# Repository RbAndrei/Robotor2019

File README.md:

# Robotor2019
Robot electric schematics, PCBs and programs for team RaSky's participating robots in the international phase of Robotor.
Electric schematics and PCBs are made in KiCad, version 5.1.2_2 for 64-bit Windows, available for free at http://www.kicad-pcb.org/
Code written in the C programming language, with the help of the Arduino IDE, version 1.8.9 for Windows, available for free at https://www.arduino.cc/en/main/software

Everything made by the team members Casapu Denis Cristian and Roibu Andrei on Github.

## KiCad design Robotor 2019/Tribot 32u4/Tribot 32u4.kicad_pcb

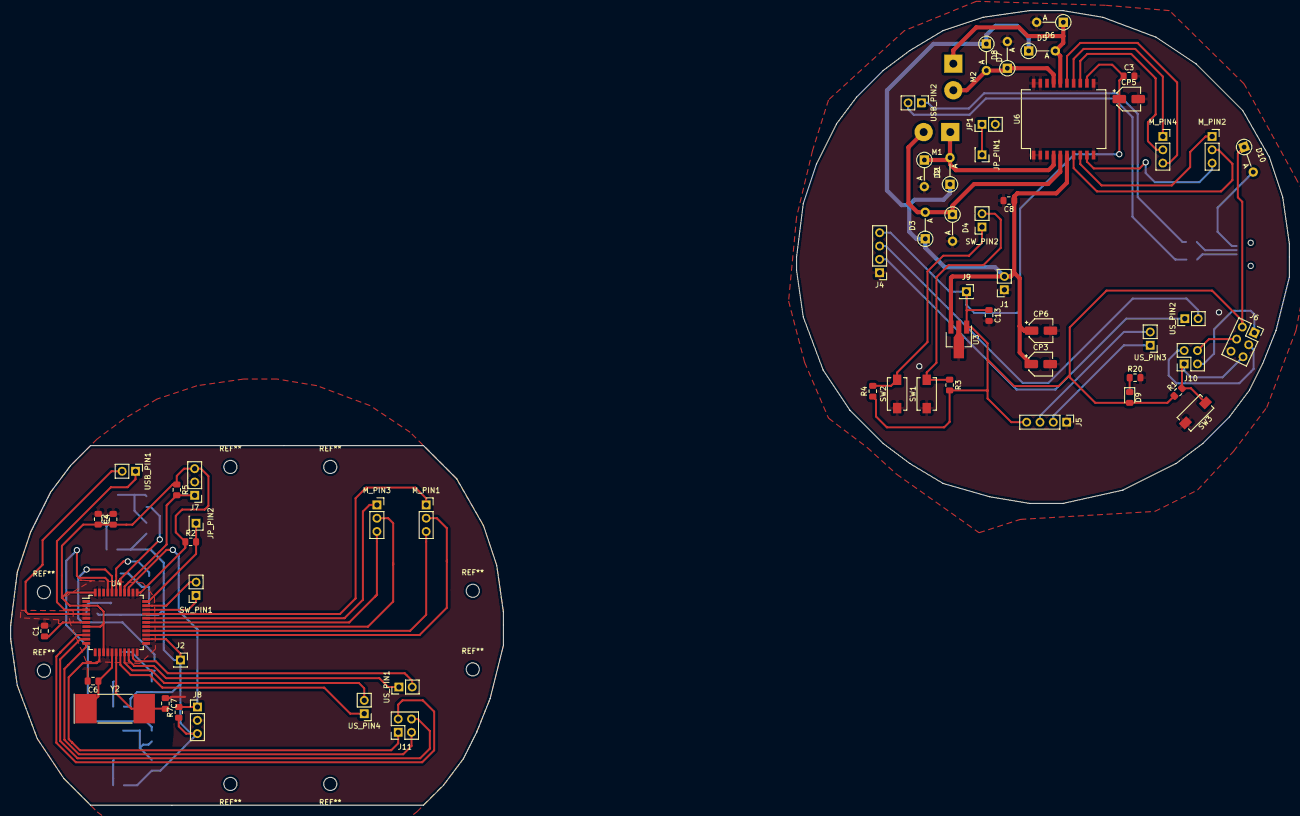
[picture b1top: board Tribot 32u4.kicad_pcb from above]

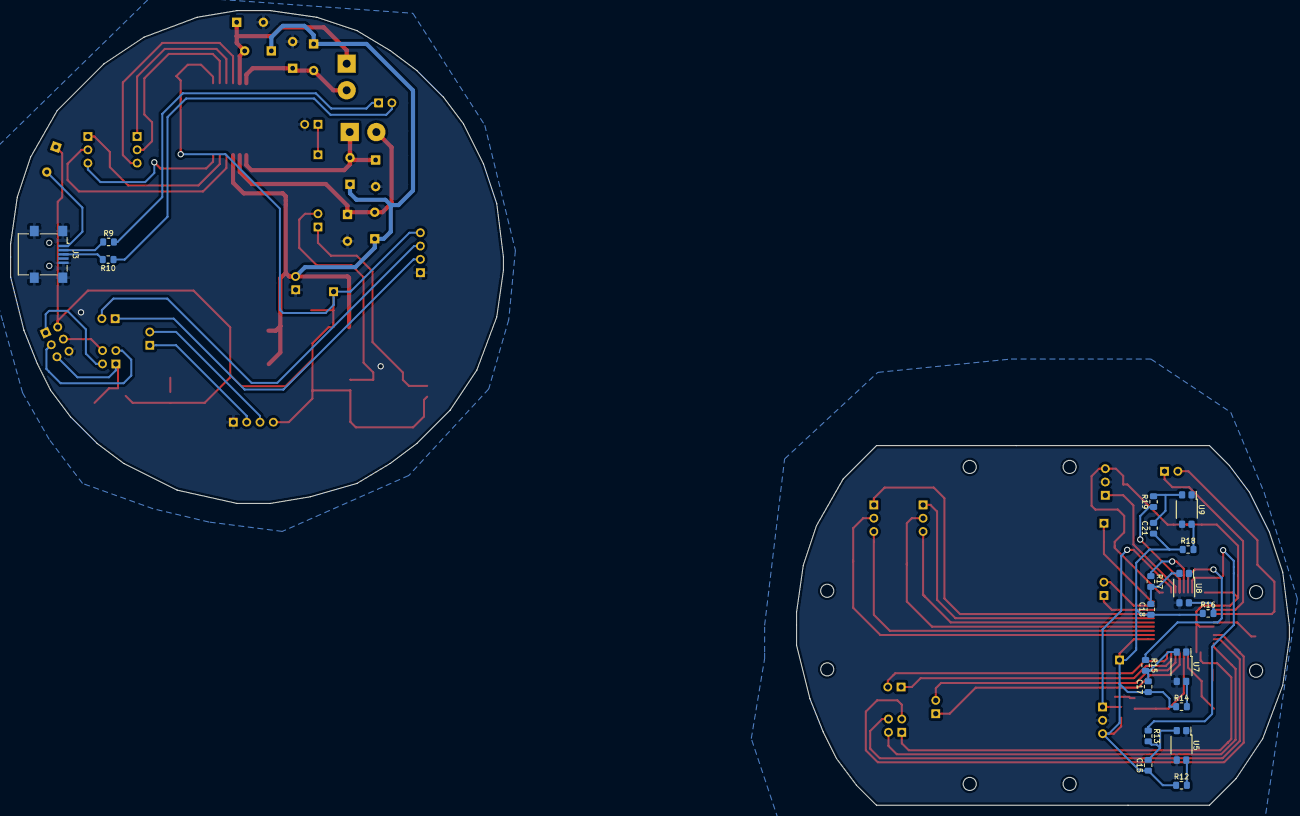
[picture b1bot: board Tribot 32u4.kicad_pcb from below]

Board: 2 copper layers, 243.9 x 151.5 mm, 81 parts (19 on the bottom side), 67 nets.

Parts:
C1: 1u; C_0805_2012Metric_Pad1.15x1.40mm_HandSolder
C2, C3, C4, C8, C13: 100n; C_0805_2012Metric_Pad1.15x1.40mm_HandSolder
C6, C7: 22p; C_0805_2012Metric_Pad1.15x1.40mm_HandSolder
C15, C17, C18, C21: 10n; C_0805_2012Metric_Pad1.15x1.40mm_HandSolder
CP3: 10uF; CP_Elec_4x5.3
CP5, CP6: 100uF; CP_Elec_4x5.3
D1, D2, D3, D4, D5, D6, D7, D8, D10: D; D_A-405_P5.08mm_Vertical_AnodeUp
D9: LED; LED_0805_2012Metric_Pad1.15x1.40mm_HandSolder
J1: Conn_01x03_Male; PinSocket_1x02_P2.54mm_Vertical
J2, J9: Conn_01x01; PinSocket_1x01_P2.54mm_Vertical
J3: USB_B_Mini; USB_Mini-B_Lumberg_2486_01_Horizontal
J4, J5: Conn_01x04_Female; PinHeader_1x04_P2.54mm_Vertical
J6: AVR-ISP-6; PinSocket_2x03_P2.54mm_Vertical
J7, J8: Conn_01x03_Female; PinHeader_1x03_P2.54mm_Vertical
J10, J11: Conn_01x04; PinSocket_2x02_P2.54mm_Vertical
JP1: Jumper; PinHeader_1x02_P2.54mm_Vertical
JP_PIN1, JP_PIN2: Conn_01x01; PinSocket_1x01_P2.54mm_Vertical
M1, M2: Motor_DC; SolderWirePad_1x02_P5.08mm_Drill1.5mm
M_PIN1, M_PIN2, M_PIN3, M_PIN4: Conn_01x03; PinSocket_1x03_P2.54mm_Vertical
R1, R3, R4: 10K; R_0805_2012Metric_Pad1.15x1.40mm_HandSolder
R2, R5, R7, R20: 1K; R_0805_2012Metric_Pad1.15x1.40mm_HandSolder
R9, R10: 22; R_0805_2012Metric_Pad1.15x1.40mm_HandSolder
R12, R13, R14, R15, R16, R17, R18, R19: 220; R_0805_2012Metric_Pad1.15x1.40mm_HandSolder
SW1, SW2, SW3: SW_Push; SW_SPST_EVQPE1
SW_PIN1, SW_PIN2: Conn_01x02; PinSocket_1x02_P2.54mm_Vertical
U3: AMS1117-5.0; SOT-89-3_Handsoldering
U4: ATMEGA32U4-AU; TQFP-44_10x10mm_P0.8mm
U5, U7, U8, U9: ITR8307; Everlight_ITR8307
U6: L298P; HSOP-20-1EP_11.0x15.9mm_P1.27mm_SlugUp
USB_PIN1, USB_PIN2: Conn_01x02; PinHeader_1x02_P2.54mm_Vertical
US_PIN1, US_PIN2, US_PIN3, US_PIN4: Conn_01x02; PinHeader_1x02_P2.54mm_Vertical
Y2: 8Mhz; Crystal_SMD_SeikoEpson_MA505-2Pin_12.7x5.1mm

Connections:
5V: C2.1, C4.2, C15.1, C17.1, C18.1, C21.1, J2.1, J7.3, J8.3, R2.1, R5.1, R7.1, R12.1, R14.1, R16.1, R18.1, U4.2, U4.7, U4.14, U4.24, U4.34, U4.44
+5V: C3.1, C13.1, CP5.1, D9.2, D10.1, J4.4, J5.4, J6.2, J9.1, R1.1, R3.2, R4.1, U3.1, U6.12
+7.5V: C8.1, CP3.1, CP6.1, D1.1, D3.1, D5.1, D7.1, J1.2, U3.3, U6.6
CRYSTAL1: C7.2, U4.17, Y2.2
CRYSTAL2: C6.1, U4.16, Y2.1
EnA: M_PIN2.1, U6.8
EnA_B: M_PIN1.1, U4.30
EnB: M_PIN4.1, U6.14
EnB_B: M_PIN3.1, U4.29
GND: C1.2, C2.2, C3.2, C4.1, C6.2, C7.1, C8.2, C13.2, CP3.2, CP5.2, CP6.2, D2.2, D4.2, D6.2, D8.2, J1.1, J3.5, J3.6, J4.1, J5.1, J6.6, J7.2, J8.2, JP1.2, R20.2, SW1.1, SW2.1, SW3.2, U3.2, U4.5, U4.15, U4.23, U4.35, U4.43, U5.1, U5.4, U6.1, U6.2, U6.10, U6.11, U6.19, U6.20, U7.1, U7.4, U8.1, U8.4, U9.1, U9.4
H1: J8.1, R7.2, U4.36
H2: J7.1, R5.2, U4.37
HWB: JP_PIN2.1, R2.2, U4.33
M1IN1: M_PIN2.2, U6.7
M1IN1_B: M_PIN1.2, U4.25
M1IN2: M_PIN2.3, U6.9
M1IN2_B: M_PIN1.3, U4.26
M2IN1: M_PIN4.2, U6.13
M2IN1_B: M_PIN3.2, U4.27
M2IN2: M_PIN4.3, U6.15
M2IN2_B: M_PIN3.3, U4.28
MISO: J6.1, J10.2
MISO_B: J11.2, U4.11
MOSI: J6.4, J10.4
MOSI_B: J11.4, U4.10
unnamed: C1.1, U4.6
unnamed: C15.2, R13.2, U5.3
unnamed: C17.2, R15.2, U7.3
unnamed: C18.2, R17.2, U8.3
unnamed: C21.2, R19.2, U9.3
unnamed: D1.2, D2.1, M1.1, U6.4
unnamed: D3.2, D4.1, M1.2, U6.5
unnamed: D5.2, D6.1, M2.1, U6.16
unnamed: D7.2, D8.1, M2.2, U6.17
unnamed: D9.1, R20.1
unnamed: D10.2, J3.1
unnamed: J3.2, R9.1
unnamed: J3.3, R10.2
unnamed: JP1.1, JP_PIN1.1
unnamed: R3.1, SW1.2, SW_PIN2.2
unnamed: R4.2, SW2.2, SW_PIN2.1
unnamed: R12.2, U5.2
unnamed: R14.2, U7.2
unnamed: R16.2, U8.2
unnamed: R18.2, U9.2
unnamed: SW_PIN1.1, U4.31
unnamed: SW_PIN1.2, U4.32
RST: J6.5, J10.1, R1.2, SW3.1
RST_B: J11.1, U4.13
S1: R13.1, U4.41
S2: R15.1, U4.40
S3: R17.1, U4.39
S4: R19.1, U4.38
SCK: J6.3, J10.3
SCK_B: J11.3, U4.9
US1P_IN: U4.21, US_PIN1.2
US1P_OUT: U4.20, US_PIN1.1
US1_IN: J4.3, US_PIN2.2
US1_OUT: J4.2, US_PIN2.1
US2P_IN: U4.19, US_PIN4.2
US2P_OUT: U4.18, US_PIN4.1
US2_IN: J5.3, US_PIN3.2
US2_OUT: J5.2, US_PIN3.1
USB+: U4.4, USB_PIN1.2
USB++: R10.1, USB_PIN2.2
USB-: U4.3, USB_PIN1.1
USB--: R9.2, USB_PIN2.1

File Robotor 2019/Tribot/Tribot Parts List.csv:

"Id";"Designator";"Package";"Quantity";"Designation";"Supplier and ref";
1;"M_PIN1,M_PIN3,M_PIN2,M_PIN4";"PinSocket_1x03_P2.54mm_Vertical";4;"Conn_01x03";;;
2;"REF**,REF**,REF**,REF**,REF**,REF**,REF**,REF**";"MountingHole_2.5mm";8;"MountingHole_2.5mm";;;
3;"D10,D1,D2,D3,D4,D5,D6,D7,D8";"D_A-405_P5.08mm_Vertical_AnodeUp";9;"D";;;
4;"C4,C5";"C_0805_2012Metric_Pad1.15x1.40mm_HandSolder";2;"10p";;;
5;"U5,U9,U8,U7";"Everlight_ITR8307";4;"ITR8307";;;
6;"BOOT_PIN1,BOOT_PIN2,PRGRM_PIN1,PRGRM_PIN2,US_PIN1,US_PIN2,US_PIN3,US_PIN4,USB_PIN1,USB_PIN2";"PinHeader_1x02_P2.54mm_Vertical";10;"Conn_01x02";;;
7;"C1,C2,C3,C8,C9,C13";"C_0805_2012Metric_Pad1.15x1.40mm_HandSolder";6;"100n";;;
8;"C6,C7";"C_0805_2012Metric_Pad1.15x1.40mm_HandSolder";2;"22p";;;
9;"C15,C17,C18,C21";"C_0805_2012Metric_Pad1.15x1.40mm_HandSolder";4;"10n";;;
10;"CP2,CP3";"CP_Elec_4x5.3";2;"10uF";;;
11;"CP4";"CP_Elec_4x5.3";1;"220uF";;;
12;"CP5,CP6";"CP_Elec_4x5.3";2;"100uF";;;
13;"D9";"LED_0805_2012Metric_Pad1.15x1.40mm_HandSolder";1;"LED";;;
14;"J1";"SolderWirePad_1x03_P5.715mm_Drill2mm";1;"Conn_01x03_Male";;;
15;"J2";"PinSocket_1x04_P2.54mm_Vertical";1;"Conn_01x04_Female";;;
16;"J3";"USB_Mini-B_Lumberg_2486_01_Horizontal";1;"USB_B_Mini";;;
17;"J4,J5";"PinHeader_1x04_P2.54mm_Vertical";2;"Conn_01x04_Female";;;
18;"J7,J8";"PinHeader_1x03_P2.54mm_Vertical";2;"Conn_01x03_Female";;;
19;"JP1,JP2";"PinSocket_1x02_P2.54mm_Vertical";2;"Jumper";;;
20;"M1,M2";"SolderWirePad_1x02_P5.08mm_Drill1.5mm";2;"Motor_DC";;;
21;"R1,R4,R8";"R_0805_2012Metric_Pad1.15x1.40mm_HandSolder";3;"10K";;;
22;"R2,R6,R9,R10";"R_0805_2012Metric_Pad1.15x1.40mm_HandSolder";4;"1R";;;
23;"R3";"R_0805_2012Metric_Pad1.15x1.40mm_HandSolder";1;"1K5";;;
24;"R5,R7";"R_0805_2012Metric_Pad1.15x1.40mm_HandSolder";2;"1K";;;
25;"R11";"R_0805_2012Metric_Pad1.15x1.40mm_HandSolder";1;"100k";;;
26;"R12,R13,R14,R15,R16,R17,R18,R19";"R_0805_2012Metric_Pad1.15x1.40mm_HandSolder";8;"220";;;
27;"R20";"R_0805_2012Metric_Pad1.15x1.40mm_HandSolder";1;"R";;;
28;"U1";"SOT-223-3_TabPin2";1;"AMS1117-3V3";;;
29;"U3";"SOT-223-3_TabPin2";1;"AMS1117-5.0";;;
30;"U4";"LQFP-48_7x7mm_P0.5mm";1;"STM32F103C8Tx";;;
31;"U6";"HSOP-20-1EP_11.0x15.9mm_P1.27mm_SlugUp";1;"L298P";;;
32;"Y1";"Crystal_SMD_SeikoEpson_MA505-2Pin_12.7x5.1mm";1;"32.768Khz";;;
33;"Y2";"Crystal_SMD_SeikoEpson_MA505-2Pin_12.7x5.1mm";1;"8Mhz";;;
34;"V_PIN1,V_PIN2";"SolderWirePad_1x02_P5.08mm_Drill1.5mm";2;"Conn_01x02";;;
35;"SW1,SW2";"SW_Push_1P1T_NO_6x6mm_H9.5mm";2;"SW_Push";;;
36;"SW_PIN1,SW_PIN2";"PinSocket_1x02_P2.54mm_Vertical";2;"Conn_01x02";;;

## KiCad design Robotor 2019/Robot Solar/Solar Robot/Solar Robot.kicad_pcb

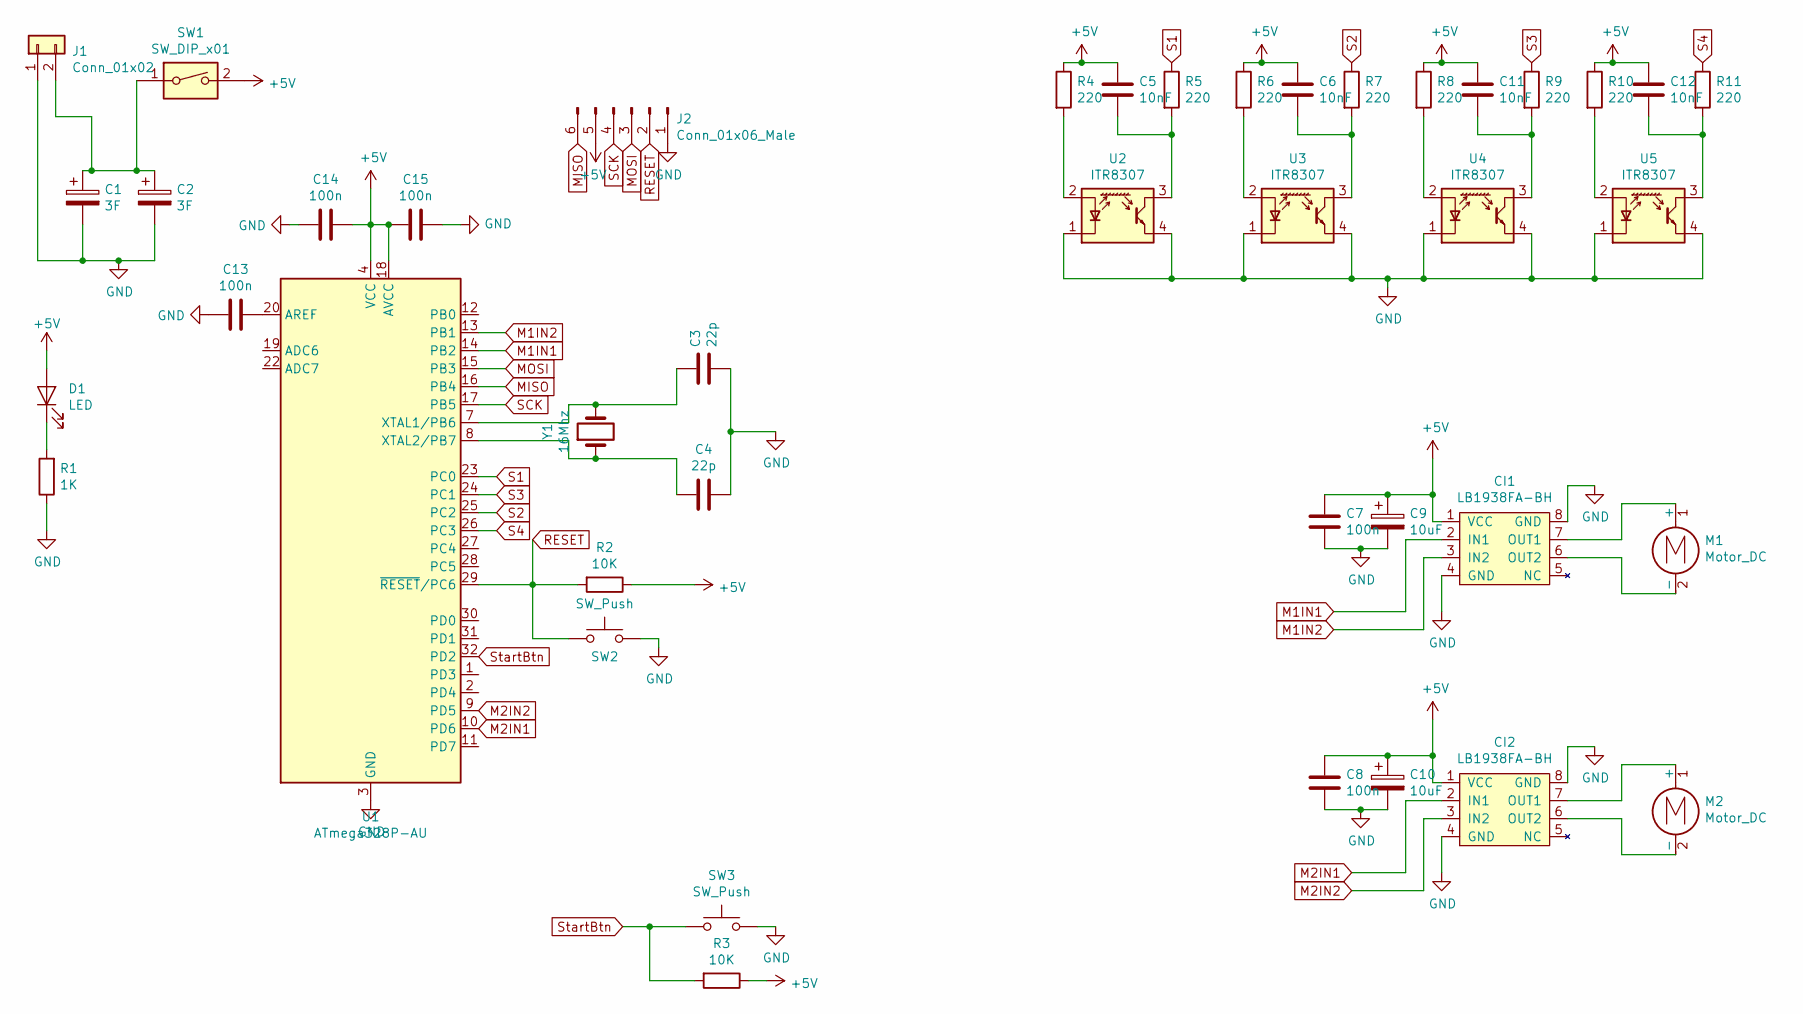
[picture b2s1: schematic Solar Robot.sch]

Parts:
C1, C2: 3F; CP_Radial_D8.0mm_P5.00mm
C3, C4: 22p; C_0805_2012Metric_Pad1.15x1.40mm_HandSolder
C5, C6, C11, C12: 10nF; C_0805_2012Metric_Pad1.15x1.40mm_HandSolder
C7, C8, C13, C14, C15: 100n; C_0805_2012Metric_Pad1.15x1.40mm_HandSolder
C9, C10: 10uF; CP_Elec_4x5.3
CI1, CI2: LB1938FA-BH; OnSemi_Micro8
D1: LED; LED_0805_2012Metric_Pad1.15x1.40mm_HandSolder
J1: Conn_01x02; SolderWirePad_1x02_P7.62mm_Drill2mm
J2: Conn_01x06_Male; PinSocket_2x03_P2.54mm_Vertical
M1, M2: Motor_DC; SolderWirePad_1x02_P5.08mm_Drill1.5mm
R1: 1K; R_0805_2012Metric_Pad1.15x1.40mm_HandSolder
R2, R3: 10K; R_0805_2012Metric_Pad1.15x1.40mm_HandSolder
R4, R5, R6, R7, R8, R9, R10, R11: 220; R_0805_2012Metric_Pad1.15x1.40mm_HandSolder
SW1: SW_DIP_x01; SolderWirePad_1x02_P5.08mm_Drill1.5mm
SW2, SW3: SW_Push; SW_SPST_CK_RS282G05A3
U1: ATmega328P-AU; TQFP-32_7x7mm_P0.8mm
U2, U3, U4, U5: ITR8307; Everlight_ITR8307
Y1: 16Mhz; Crystal_SMD_SeikoEpson_MA505-2Pin_12.7x5.1mm_HandSoldering

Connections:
+5V: C5.1, C6.1, C7.2, C8.2, C9.1, C10.1, C11.1, C12.1, C14.1, C15.2, CI1.1 (VCC), CI2.1 (VCC), D1.2 (A), J2.5, R2.1, R3.1, R4.1, R6.1, R8.1, R10.1, SW1.2, U1.4 (VCC), U1.6 (VCC), U1.18 (AVCC); also elsewhere on the board
GND: C1.2, C2.2, C3.2, C4.1, C7.1, C8.1, C9.2, C10.2, C13.2, C14.2, C15.1, CI1.4 (GND), CI1.8 (GND), CI2.4 (GND), CI2.8 (GND), J1.1, J2.1, R1.1, SW2.2, SW3.2, U1.3 (GND), U1.5 (GND), U1.21 (GND), U2.1 (K), U2.4 (E), U3.1 (K), U3.4 (E), U4.1 (K), U4.4 (E), U5.1 (K), U5.4 (E)
M1IN1: CI1.2 (IN1), U1.14 (PB2)
M1IN2: CI1.3 (IN2), U1.13 (PB1)
M2IN1: CI2.2 (IN1), U1.10 (PD6)
M2IN2: CI2.3 (IN2), U1.9 (PD5)
MISO: J2.6, U1.16 (PB4)
MOSI: J2.3, U1.15 (PB3)
unnamed: C1.1, C2.1, J1.2, SW1.1
unnamed: C3.1, U1.7 (XTAL1/PB6), Y1.2
unnamed: C4.2, U1.8 (XTAL2/PB7), Y1.1
unnamed 11: C5.2, R5.2, U2.3 (C); also elsewhere on the board
unnamed 12: C6.2, R7.2, U3.3 (C); also elsewhere on the board
unnamed 13: C11.2, R9.2, U4.3 (C); also elsewhere on the board
unnamed 14: C12.2, R11.2, U5.3 (C); also elsewhere on the board
unnamed: C13.1, U1.20 (AREF)
unnamed: CI1.6 (OUT2), M1.2 (-)
unnamed: CI1.7 (OUT1), M1.1 (+)
unnamed: CI2.6 (OUT2), M2.2 (-)
unnamed: CI2.7 (OUT1), M2.1 (+)
unnamed: D1.1 (K), R1.2
unnamed: R4.2, U2.2 (A)
unnamed: R6.2, U3.2 (A)
unnamed: R8.2, U4.2 (A)
unnamed: R10.2, U5.2 (A)
RESET: J2.2, R2.2, SW2.1, U1.29 (~RESET~/PC6)
S1: R5.1, U1.23 (PC0)
S2: R7.1, U1.25 (PC2)
S3: R9.1, U1.24 (PC1)
S4: R11.1, U1.26 (PC3)
SCK: J2.4, U1.17 (PB5)
StartBtn: R3.2, SW3.1, U1.32 (PD2)

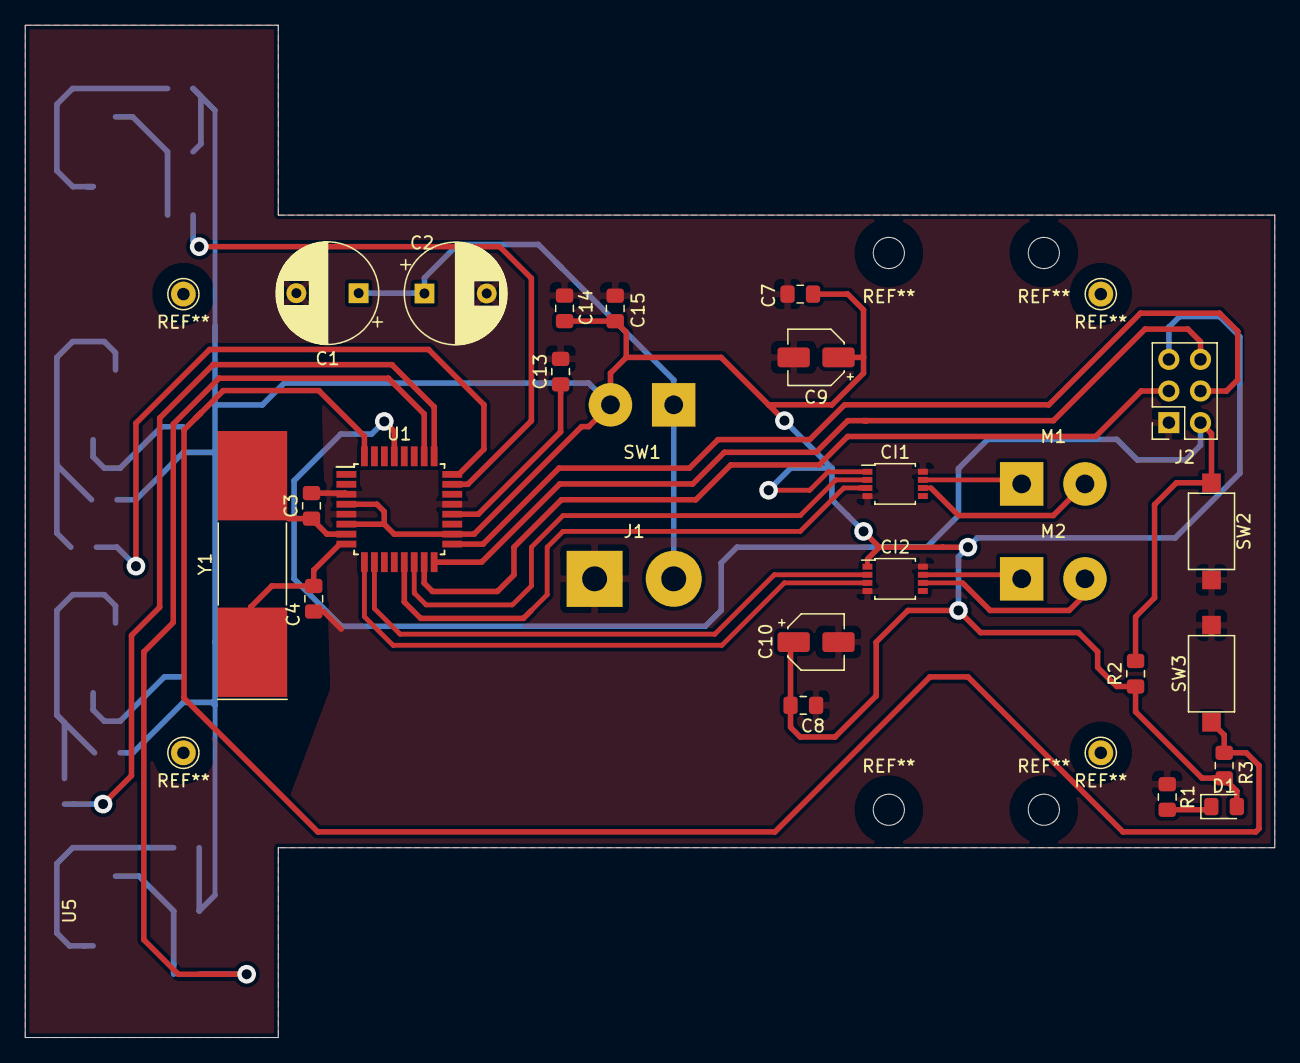
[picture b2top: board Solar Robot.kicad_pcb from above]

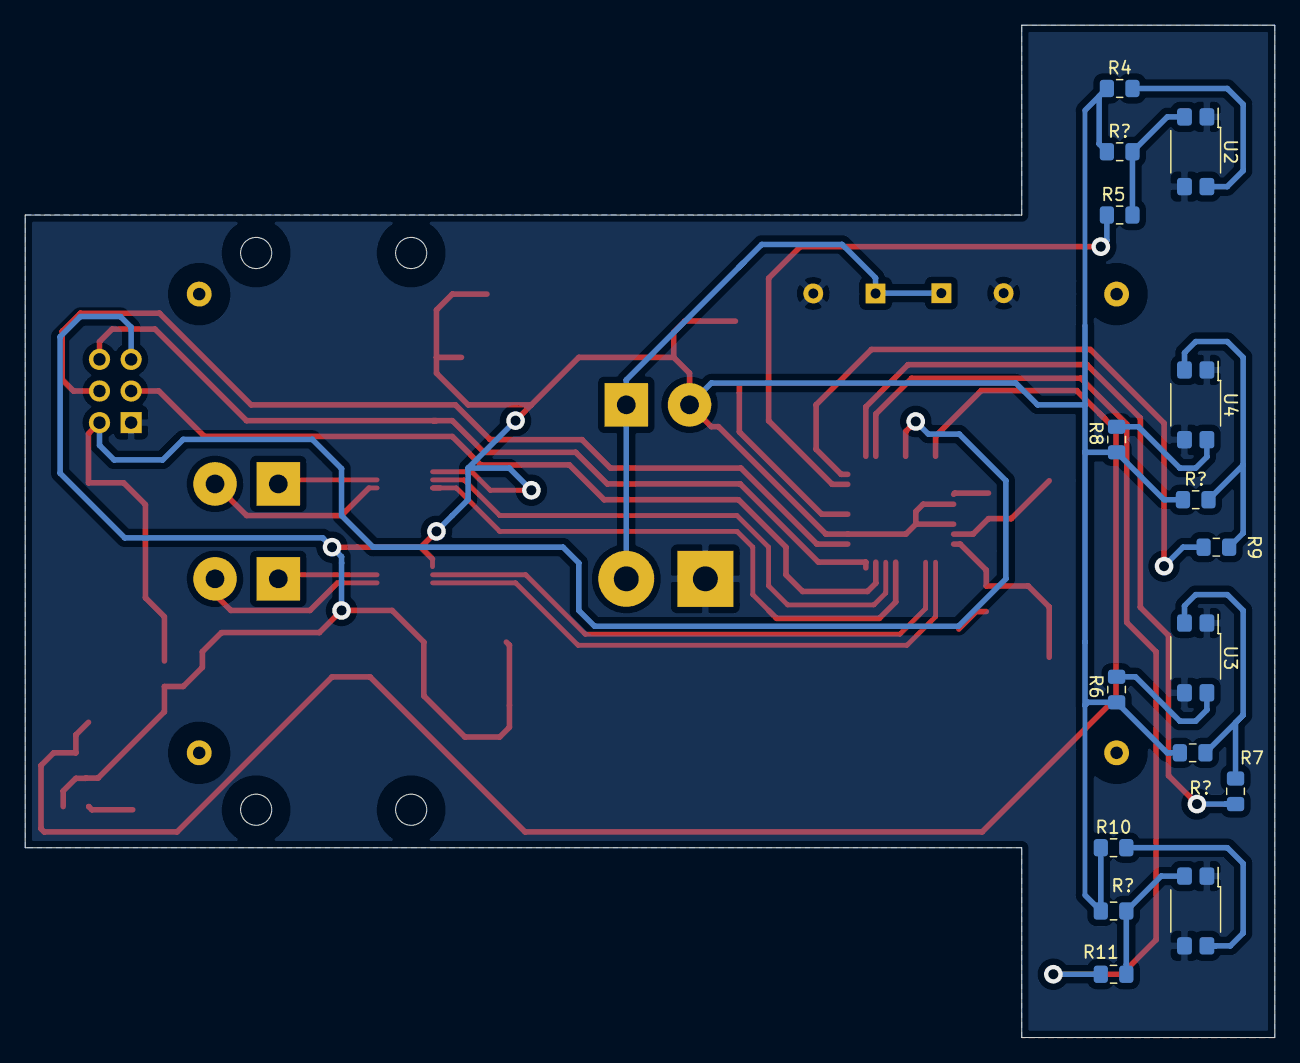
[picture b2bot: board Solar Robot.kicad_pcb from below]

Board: 2 copper layers, 100.3 x 81.3 mm, 42 parts (16 on the bottom side), 32 nets.

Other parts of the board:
R?: 47K; C_0805_2012Metric_Pad1.15x1.40mm_HandSolder
R?#2, R?#3, R?#4: 47K; C_0805_2012Metric_Pad1.15x1.40mm_HandSolder

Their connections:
+5V: R?.1, R?#2.1, R?#3.1, R?#4.1; also elsewhere on the board
unnamed 11: R?.2; also elsewhere on the board
unnamed 12: R?#2.2; also elsewhere on the board
unnamed 13: R?#3.2; also elsewhere on the board
unnamed 14: R?#4.2; also elsewhere on the board

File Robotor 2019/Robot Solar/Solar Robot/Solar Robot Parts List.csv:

"Id";"Designator";"Package";"Quantity";"Designation";"Supplier and ref";
1;"REF**,REF**,REF**,REF**";"Pin_D1.0mm_L10.0mm";4;"Pin_D1.0mm_L10.0mm";;;
2;"REF**,REF**,REF**,REF**";"MountingHole_2.5mm";4;"MountingHole_2.5mm";;;
3;"U2,U5,U3,U4";"Everlight_ITR8307";4;"ITR8307";;;
4;"C1,C2";"CP_Radial_D8.0mm_P5.00mm";2;"3F";;;
5;"C3,C4";"C_0805_2012Metric_Pad1.15x1.40mm_HandSolder";2;"22p";;;
6;"C5,C6,C11,C12";"C_0805_2012Metric_Pad1.15x1.40mm_HandSolder";4;"10nF";;;
7;"C7,C8";"C_0805_2012Metric_Pad1.15x1.40mm_HandSolder";2;"100n";;;
8;"C9,C10";"CP_Elec_4x5.3";2;"10uF";;;
9;"CI1,CI2";"OnSemi_Micro8";2;"LB1938FA-BH";;;
10;"D1";"LED_0805_2012Metric_Pad1.15x1.40mm_HandSolder";1;"LED";;;
11;"J1";"SolderWirePad_1x02_P7.62mm_Drill2mm";1;"Conn_01x02";;;
12;"J2";"PinHeader_1x06_P2.54mm_Vertical";1;"Conn_01x06_Male";;;
13;"M1,M2";"SolderWirePad_1x02_P5.08mm_Drill1.5mm";2;"Motor_DC";;;
14;"R1";"R_0805_2012Metric_Pad1.15x1.40mm_HandSolder";1;"1K";;;
15;"R2,R3";"R_0805_2012Metric_Pad1.15x1.40mm_HandSolder";2;"10K";;;
16;"R4,R5,R6,R7,R8,R9,R10,R11";"R_0805_2012Metric_Pad1.15x1.40mm_HandSolder";8;"220";;;
17;"SW1";"SolderWirePad_1x02_P5.08mm_Drill1.5mm";1;"SW_DIP_x01";;;
18;"SW2,SW3";"SW_Push_1P1T_NO_6x6mm_H9.5mm";2;"SW_Push";;;
19;"U1";"TQFP-32_7x7mm_P0.8mm";1;"ATmega328-PU";;;
20;"Y1";"Crystal_SMD_SeikoEpson_MA505-2Pin_12.7x5.1mm_HandSoldering";1;"16Mhz";;;

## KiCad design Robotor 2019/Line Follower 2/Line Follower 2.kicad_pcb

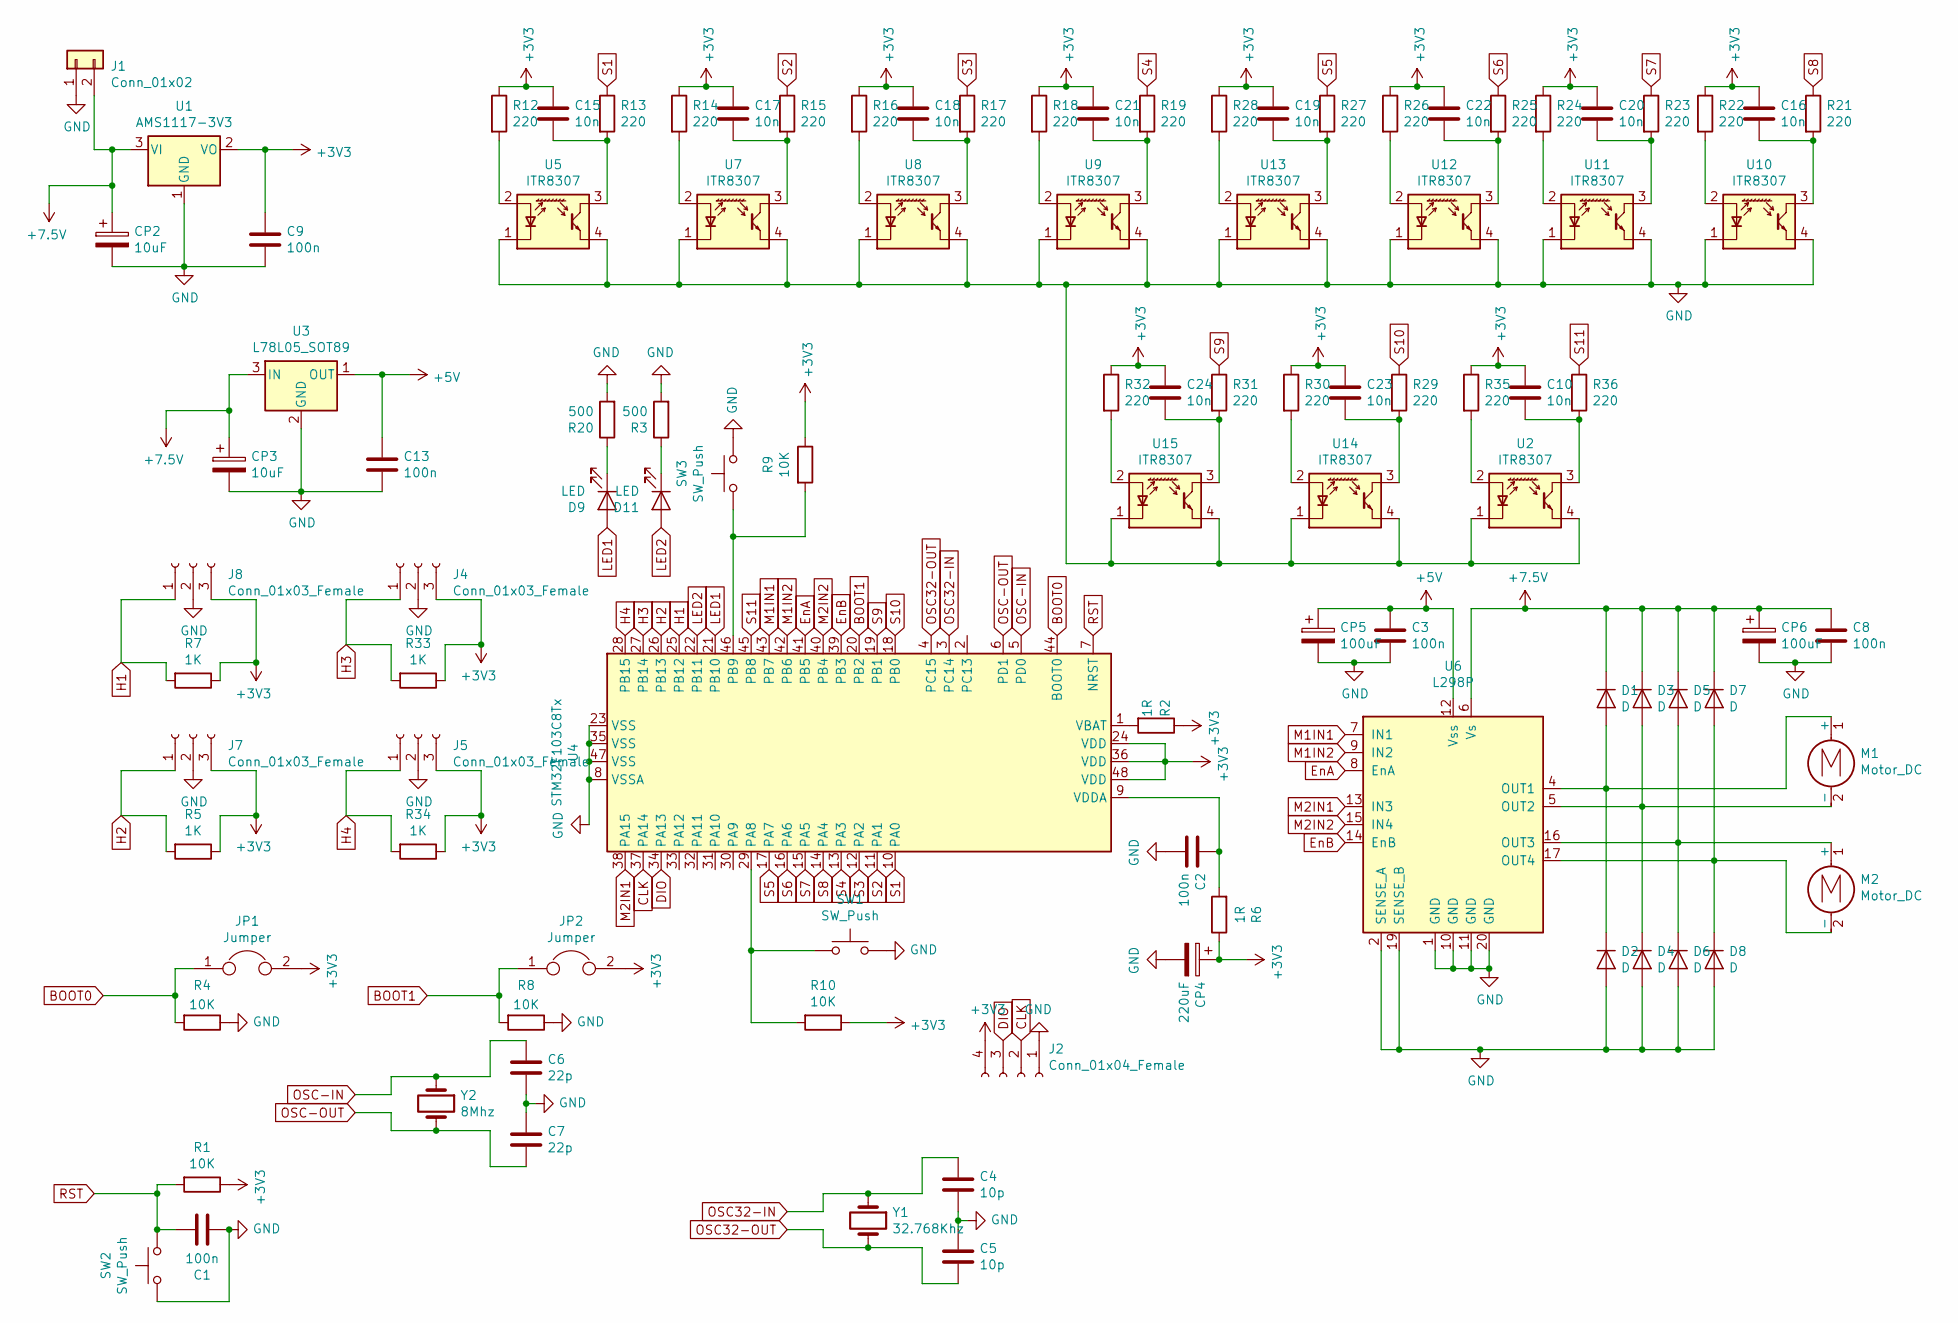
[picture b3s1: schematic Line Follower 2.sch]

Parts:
C1, C2, C3, C8, C9, C13: 100n; C_0805_2012Metric_Pad1.15x1.40mm_HandSolder
C4, C5: 10p; C_0805_2012Metric_Pad1.15x1.40mm_HandSolder
C6, C7: 22p; C_0805_2012Metric_Pad1.15x1.40mm_HandSolder
C10, C15, C16, C17, C18, C19, C20, C21, C22, C23, C24: 10n; C_0805_2012Metric_Pad1.15x1.40mm_HandSolder
CP2, CP3: 10uF; CP_Elec_4x5.3
CP4: 220uF; CP_Elec_4x5.3
CP5, CP6: 100uF; CP_Elec_10x10
D1, D2, D3, D4, D5, D6, D7, D8: D; D_1206_3216Metric_Pad1.42x1.75mm_HandSolder
D9, D11: LED; LED_0805_2012Metric_Pad1.15x1.40mm_HandSolder
J1: Conn_01x02; PinSocket_1x02_P2.54mm_Vertical
J2: Conn_01x04_Female; PinSocket_1x04_P2.54mm_Vertical
J4, J5, J7, J8: Conn_01x03_Female; PinHeader_1x03_P2.54mm_Vertical
JP1, JP2: Jumper; PinSocket_1x02_P2.54mm_Vertical
M1, M2: Motor_DC; SolderWirePad_1x02_P5.08mm_Drill1.5mm
R1, R4, R8, R9, R10: 10K; R_0805_2012Metric_Pad1.15x1.40mm_HandSolder
R2: 1R; R_1206_3216Metric_Pad1.42x1.75mm_HandSolder
R3, R20: 500; R_0805_2012Metric_Pad1.15x1.40mm_HandSolder
R5, R7, R33, R34: 1K; R_0805_2012Metric_Pad1.15x1.40mm_HandSolder
R6: 1R; R_0805_2012Metric_Pad1.15x1.40mm_HandSolder
R12, R13, R14, R15, R16, R17, R18, R19, R21, R22, R23, R24, R25, R26, R27, R28, R29, R30, R31, R32, R35, R36: 220; R_1206_3216Metric_Pad1.42x1.75mm_HandSolder
SW1, SW2, SW3: SW_Push; SW_SPST_CK_RS282G05A3
U1: AMS1117-3V3; SOT-223-3_TabPin2
U2, U5, U7, U8, U9, U10, U11, U12, U13, U14, U15: ITR8307; Everlight_ITR8307
U3: L78L05_SOT89; SOT-89-3_Handsoldering
U4: STM32F103C8Tx; LQFP-48_7x7mm_P0.5mm
U6: L298P; HSOP-20-1EP_11.0x15.9mm_P1.27mm_SlugUp
Y1: 32.768Khz; Crystal_SMD_0603-2Pin_6.0x3.5mm_HandSoldering
Y2: 8Mhz; Crystal_SMD_SeikoEpson_MA505-2Pin_12.7x5.1mm

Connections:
+3V3: C9.1, C10.1, C15.1, C16.1, C17.1, C18.1, C19.1, C20.1, C21.1, C22.1, C23.1, C24.1, CP4.1, J2.4, J4.3, J5.3, J7.3, J8.3, JP1.2, JP2.2, R1.1, R2.1, R5.1, R6.1, R7.1, R9.1, R10.1, R12.1, R14.1, R16.1, R18.1, R22.1, R24.1, R26.1, R28.1, R30.1, R32.1, R33.1, R34.1, R35.1, U1.2 (VO), U4.24 (VDD), U4.36 (VDD), U4.48 (VDD)
+5V: C3.1, C13.1, CP5.1, U3.1 (OUT), U6.12 (Vss)
+7.5V: C8.1, CP2.1, CP3.1, CP6.1, D1.1 (K), D3.1 (K), D5.1 (K), D7.1 (K), J1.2, U1.3 (VI), U3.3 (IN), U6.6 (Vs)
BOOT0: JP1.1, R4.2, U4.44 (BOOT0)
BOOT1: JP2.1, R8.2, U4.20 (PB2)
CLK: J2.2, U4.37 (PA14)
DIO: J2.3, U4.34 (PA13)
EnA: U4.41 (PB5), U6.8 (EnA)
EnB: U4.39 (PB3), U6.14 (EnB)
GND: C1.1, C2.2, C3.2, C4.2, C5.1, C6.2, C7.1, C8.2, C9.2, C13.2, CP2.2, CP3.2, CP4.2, CP5.2, CP6.2, D2.2 (A), D4.2 (A), D6.2 (A), D8.2 (A), J1.1, J2.1, J4.2, J5.2, J7.2, J8.2, R3.2, R4.1, R8.1, R20.2, SW1.2, SW2.1, SW3.2, U1.1 (GND), U2.1 (K), U2.4 (E), U3.2 (GND), U4.8 (VSSA), U4.23 (VSS), U4.35 (VSS), U4.47 (VSS), U5.1 (K), U5.4 (E), U6.1 (GND), U6.2 (SENSE_A), U6.10 (GND), U6.11 (GND), U6.19 (SENSE_B), U6.20 (GND), U7.1 (K), U7.4 (E), U8.1 (K), U8.4 (E), U9.1 (K), U9.4 (E), U10.1 (K), U10.4 (E), U11.1 (K), U11.4 (E), U12.1 (K), U12.4 (E), U13.1 (K), U13.4 (E), U14.1 (K), U14.4 (E), U15.1 (K), U15.4 (E)
H1: J8.1, R7.2, U4.25 (PB12)
H2: J7.1, R5.2, U4.26 (PB13)
H3: J4.1, R33.2, U4.27 (PB14)
H4: J5.1, R34.2, U4.28 (PB15)
LED1: D9.2 (A), U4.21 (PB10)
LED2: D11.2 (A), U4.22 (PB11)
M1IN1: U4.43 (PB7), U6.7 (IN1)
M1IN2: U4.42 (PB6), U6.9 (IN2)
M2IN1: U4.38 (PA15), U6.13 (IN3)
M2IN2: U4.40 (PB4), U6.15 (IN4)
unnamed: C2.1, R6.2, U4.9 (VDDA)
unnamed: C10.2, R36.2, U2.3 (C)
unnamed: C15.2, R13.2, U5.3 (C)
unnamed: C16.2, R21.2, U10.3 (C)
unnamed: C17.2, R15.2, U7.3 (C)
unnamed: C18.2, R17.2, U8.3 (C)
unnamed: C19.2, R27.2, U13.3 (C)
unnamed: C20.2, R23.2, U11.3 (C)
unnamed: C21.2, R19.2, U9.3 (C)
unnamed: C22.2, R25.2, U12.3 (C)
unnamed: C23.2, R29.2, U14.3 (C)
unnamed: C24.2, R31.2, U15.3 (C)
unnamed: D1.2 (A), D2.1 (K), M1.1 (+), U6.4 (OUT1)
unnamed: D3.2 (A), D4.1 (K), M1.2 (-), U6.5 (OUT2)
unnamed: D5.2 (A), D6.1 (K), M2.1 (+), U6.16 (OUT3)
unnamed: D7.2 (A), D8.1 (K), M2.2 (-), U6.17 (OUT4)
unnamed: D9.1 (K), R20.1
unnamed: D11.1 (K), R3.1
unnamed: R2.2, U4.1 (VBAT)
unnamed: R9.2, SW3.1, U4.46 (PB9)
unnamed: R10.2, SW1.1, U4.29 (PA8)
unnamed: R12.2, U5.2 (A)
unnamed: R14.2, U7.2 (A)
unnamed: R16.2, U8.2 (A)
unnamed: R18.2, U9.2 (A)
unnamed: R22.2, U10.2 (A)
unnamed: R24.2, U11.2 (A)
unnamed: R26.2, U12.2 (A)
unnamed: R28.2, U13.2 (A)
unnamed: R30.2, U14.2 (A)
unnamed: R32.2, U15.2 (A)
unnamed: R35.2, U2.2 (A)
OSC32-IN: C4.1, U4.3 (PC14), Y1.1
OSC32-OUT: C5.2, U4.4 (PC15), Y1.2
OSC-IN: C6.1, U4.5 (PD0), Y2.1
OSC-OUT: C7.2, U4.6 (PD1), Y2.2
RST: C1.2, R1.2, SW2.2, U4.7 (NRST)
S1: R13.1, U4.10 (PA0)
S2: R15.1, U4.11 (PA1)
S3: R17.1, U4.12 (PA2)
S4: R19.1, U4.13 (PA3)
S5: R27.1, U4.17 (PA7)
S6: R25.1, U4.16 (PA6)
S7: R23.1, U4.15 (PA5)
S8: R21.1, U4.14 (PA4)
S9: R31.1, U4.19 (PB1)
S10: R29.1, U4.18 (PB0)
S11: R36.1, U4.45 (PB8)

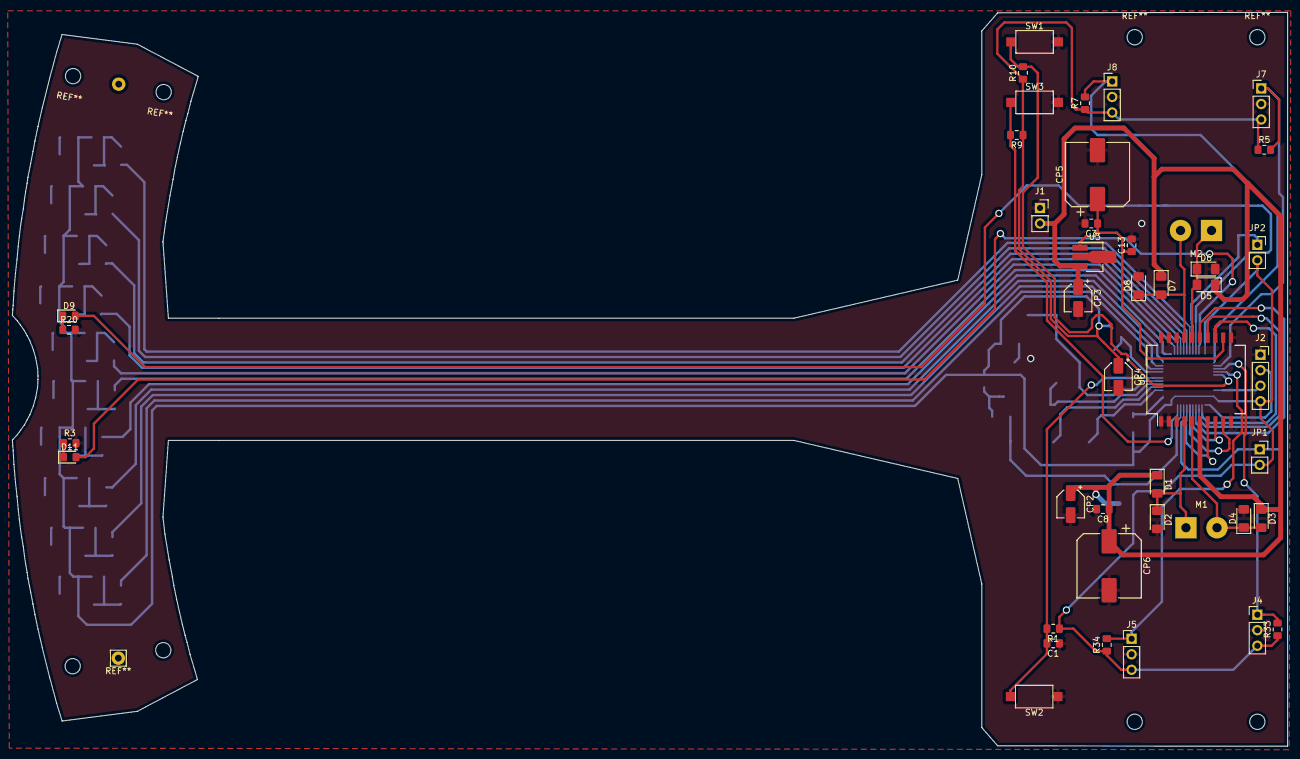
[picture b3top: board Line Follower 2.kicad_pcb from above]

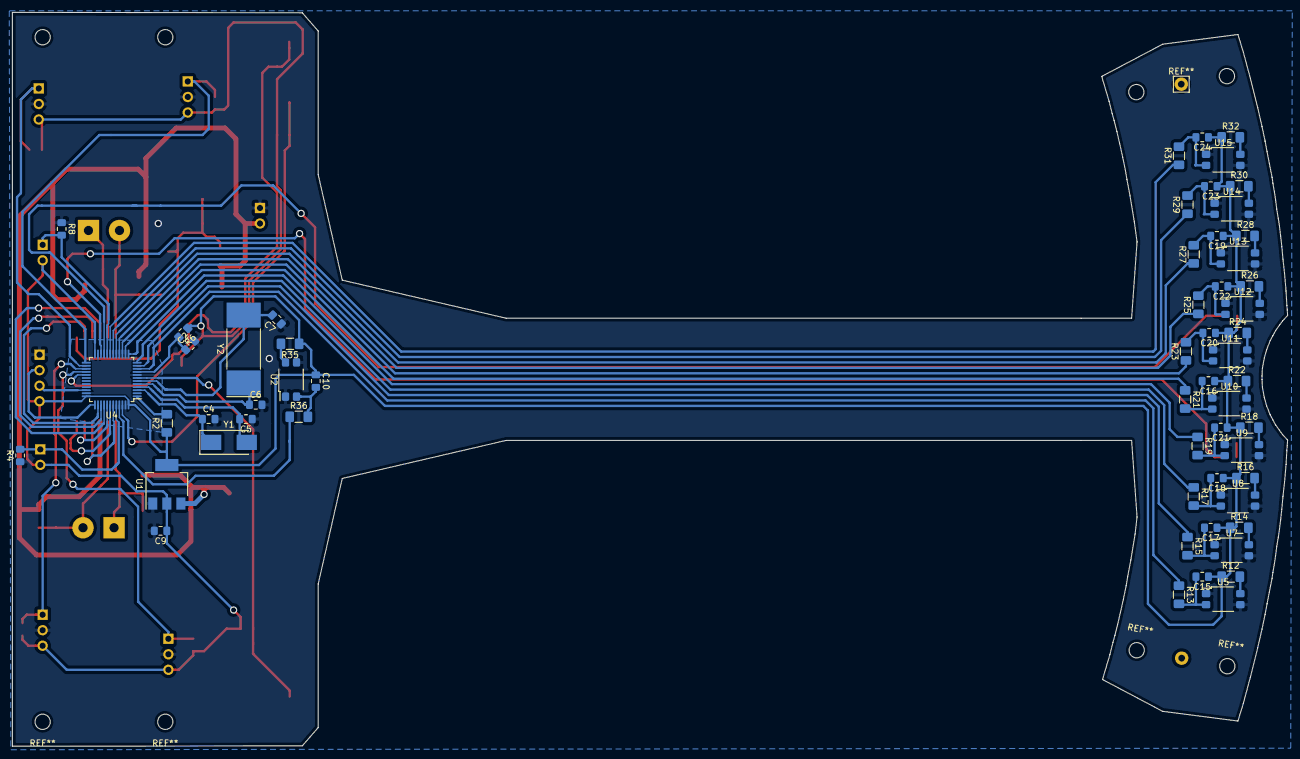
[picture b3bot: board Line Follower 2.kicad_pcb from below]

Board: 2 copper layers, 208.7 x 120.1 mm, 101 parts (58 on the bottom side), 68 nets.

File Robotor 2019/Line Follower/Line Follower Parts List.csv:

Id;Designator;Package;Quantity;Designation;Supplier and ref
1;R13,R15,R17,R19,R31,R29,R27,R25,R23,R21;R_1206_3216Metric_Pad1.42x1.75mm_HandSolder;10;220;
2;U4;LQFP-48_7x7mm_P0.5mm;1;STM32F103C8Tx;
3;REF**,REF**,REF**,REF**,REF**,REF**,REF**,REF**;MountingHole_2.5mm;8;MountingHole_2.5mm;
4;U5,U7,U8,U9,U10,U11,U12,U13,U14,U15;Everlight_ITR8307;10;ITR8307;
5;C1,C2,C3,C8,C9,C13;C_0805_2012Metric_Pad1.15x1.40mm_HandSolder;6;100n;
6;SW1;SW_Push_1P1T_NO_6x6mm_H9.5mm;1;SW_Push;
7;C4,C5;C_0805_2012Metric_Pad1.15x1.40mm_HandSolder;2;10p;
8;C6,C7;C_0805_2012Metric_Pad1.15x1.40mm_HandSolder;2;22p;
9;C15,C16,C17,C18,C19,C20,C21,C22,C23,C24;C_0805_2012Metric_Pad1.15x1.40mm_HandSolder;10;10n;
10;CP2,CP3;CP_Elec_4x5.3;2;10uF;
11;CP4;CP_Elec_4x5.3;1;220uF;
12;CP5,CP6;CP_Elec_4x5.3;2;100uF;
13;D1,D2,D3,D4,D5,D6,D7,D8,D10;D_A-405_P5.08mm_Vertical_AnodeUp;9;D;
14;D9;LED_0805_2012Metric_Pad1.15x1.40mm_HandSolder;1;LED;
15;J1;SolderWirePad_1x03_P5.715mm_Drill2mm;1;Conn_01x03_Male;
16;J2;PinSocket_1x04_P2.54mm_Vertical;1;Conn_01x04_Female;
17;J3;USB_Mini-B_Lumberg_2486_01_Horizontal;1;USB_B_Mini;
18;J4,J5,J7,J8;PinHeader_1x03_P2.54mm_Vertical;4;Conn_01x03_Female;
19;JP1,JP2;PinSocket_1x02_P2.54mm_Vertical;2;Jumper;
20;M1,M2;SolderWirePad_1x02_P5.08mm_Drill1.5mm;2;Motor_DC;
21;R1,R4,R8;R_0805_2012Metric_Pad1.15x1.40mm_HandSolder;3;10K;
22;R2,R6,R9,R10;R_0805_2012Metric_Pad1.15x1.40mm_HandSolder;4;1R;
23;R3;R_0805_2012Metric_Pad1.15x1.40mm_HandSolder;1;1K5;
24;R5,R7,R33,R34;R_0805_2012Metric_Pad1.15x1.40mm_HandSolder;4;1K;
25;R11;R_0805_2012Metric_Pad1.15x1.40mm_HandSolder;1;100k;
26;R12,R14,R16,R18,R22,R24,R26,R28,R30,R32;R_0805_2012Metric_Pad1.15x1.40mm_HandSolder;10;220;
27;R20;R_0805_2012Metric_Pad1.15x1.40mm_HandSolder;1;500;
28;U1;SOT-223-3_TabPin2;1;AMS1117-3V3;
29;U3;SOT-223-3_TabPin2;1;AMS1117-5.0;
30;U6;HSOP-20-1EP_11.0x15.9mm_P1.27mm_SlugUp;1;L298P;
31;Y1;Crystal_SMD_SeikoEpson_MA505-2Pin_12.7x5.1mm;1;32.768Khz;
32;Y2;Crystal_SMD_SeikoEpson_MA505-2Pin_12.7x5.1mm;1;8Mhz;
